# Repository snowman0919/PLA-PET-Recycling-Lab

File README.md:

# PPR — 균일 직경 필라멘트를 위한 통합 재활용기
목표와 경계는 [KODEX.md](KODEX.md), 현재 증거·작업은 [STATUS.md](STATUS.md), 압출 방법 비교는 [품질 경로 결정 기록](docs/decisions/filament-quality-route.md)을 따른다.

제품 범위: 호퍼 → S1 2축 파쇄 → 선택 이송부 → S2 편심/역자전 분쇄 → 버퍼 → 수평 압출 → 냉각/직경 계측 → 가압 인출 → 장력 분리 권취.
최종 목표는 냉각 후 일정한 1.75mm 필라멘트를 경제적으로 만드는 것이다. 현재 연결 이송과 실제 필라멘트 생산 모두 미완료다.
상류 실패와 별개로 최종 제품의 같은 압출 모듈에 건조 기준 원료를 넣는 설계/디지털 시험을 진행할 수 있다. 전체 제품 성공과는 구분한다.

## 작업 자산
- c2.1/cad/PPR_VP1.step: 전체 기계 STEP
- c2.1/cad/PPR_C2_1_machine_integration.FCStd 및 c2.1/src/: 편집 원본/생성기
- c2.1/bom/system_bom.csv, .xlsx: 활성 BOM
- c2.1/firmware/, electrical/: 제어/전장 자산
- c2.2/sim/assets/usd/full_machine.usda: 대응 Isaac 장면
- c2.2/results/full_machine/layout_comparison.json: 기준안/재배치안 비교
- tests/, c2/tests/, c2.1/tests/, c2.3/tests/: 범위별 회귀 자산

재현은 해당 생성기/실행기의 --help와 결과의 원본 해시·설정을 사용한다. CAD/STEP, 충돌 메시/USD, BOM, 시험 결과를 같은 후보로 맞춘 후 해당 verify_artifacts를 수행한다.
역사 실험의 재실행이나 Graphify 완료를 새 제품 작업의 선행조건으로 만들지 않는다. 숫자·PASS 명칭은 당시 범위에서만 유효하다.
물리 제작·구매·통전·실물시험·main 병합은 사용자 승인 전 HOLD다. MIT 및 LICENSE-HARDWARE를 유지한다.

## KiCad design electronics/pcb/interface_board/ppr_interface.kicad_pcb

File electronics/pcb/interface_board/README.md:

# PPR monitor/interface board

`ppr_interface.kicad_sch`와 `ppr_interface.kicad_pcb`는 KiCad 9 네이티브 산출물이다. `generate.py`가 source of truth이며 `fill_zones.py`는 KiCad의 pcbnew 엔진으로 분리된 FIELD_0V/GND 존을 채운다.

이 보드는 **MONITOR ONLY / NO SAFETY CREDIT / NOT FOR FABRICATION** 상태다. 안전 릴레이, 접촉기, 퓨즈, thermal fuse, heater/motor driver를 대체하지 않는다.

## 재생성

```bash
python3 -m venv /tmp/ppr-kiutils-venv
/tmp/ppr-kiutils-venv/bin/pip install -r electronics/pcb/interface_board/requirements-authoring.txt
/tmp/ppr-kiutils-venv/bin/python electronics/pcb/interface_board/generate.py
kicad-cli sch erc --exit-code-violations electronics/pcb/interface_board/ppr_interface.kicad_sch
kicad-cli pcb drc --exit-code-violations electronics/pcb/interface_board/ppr_interface.kicad_pcb
```

필수 도구는 KiCad CLI/pcbnew 9.0.9와 `kiutils==1.4.8`이다. 회로·PCB 검토 결과는 `design_review_ko.md`, 공식 URL/로컬 검토 해시는 `datasheet_evidence.json`, 제조 출력은 `fabrication/`, 육안 검토 렌더는 `review/`에 있다. 제3자 PDF 자체는 루트 정책에 따라 Git에 넣지 않는다.

## 인터페이스

- J1: 8개 24 V dry-contact 보조 입력과 중복 +24V_SENSE/FIELD_0V
- J2: Mega D22–D29 진단 입력
- J3: Mega command 입력 8개
- J4: 외부 정격 드라이버로 가는 5 V 로직 출력 8개

정확한 케이블 결선은 `design_review_ko.md`와 `electronics/pinout/mega_pinout.csv`를 함께 사용한다. 현재 pin header footprint는 기구 proof용이며 keyed/latching 커넥터 MPN 확정 전 발주 금지다.

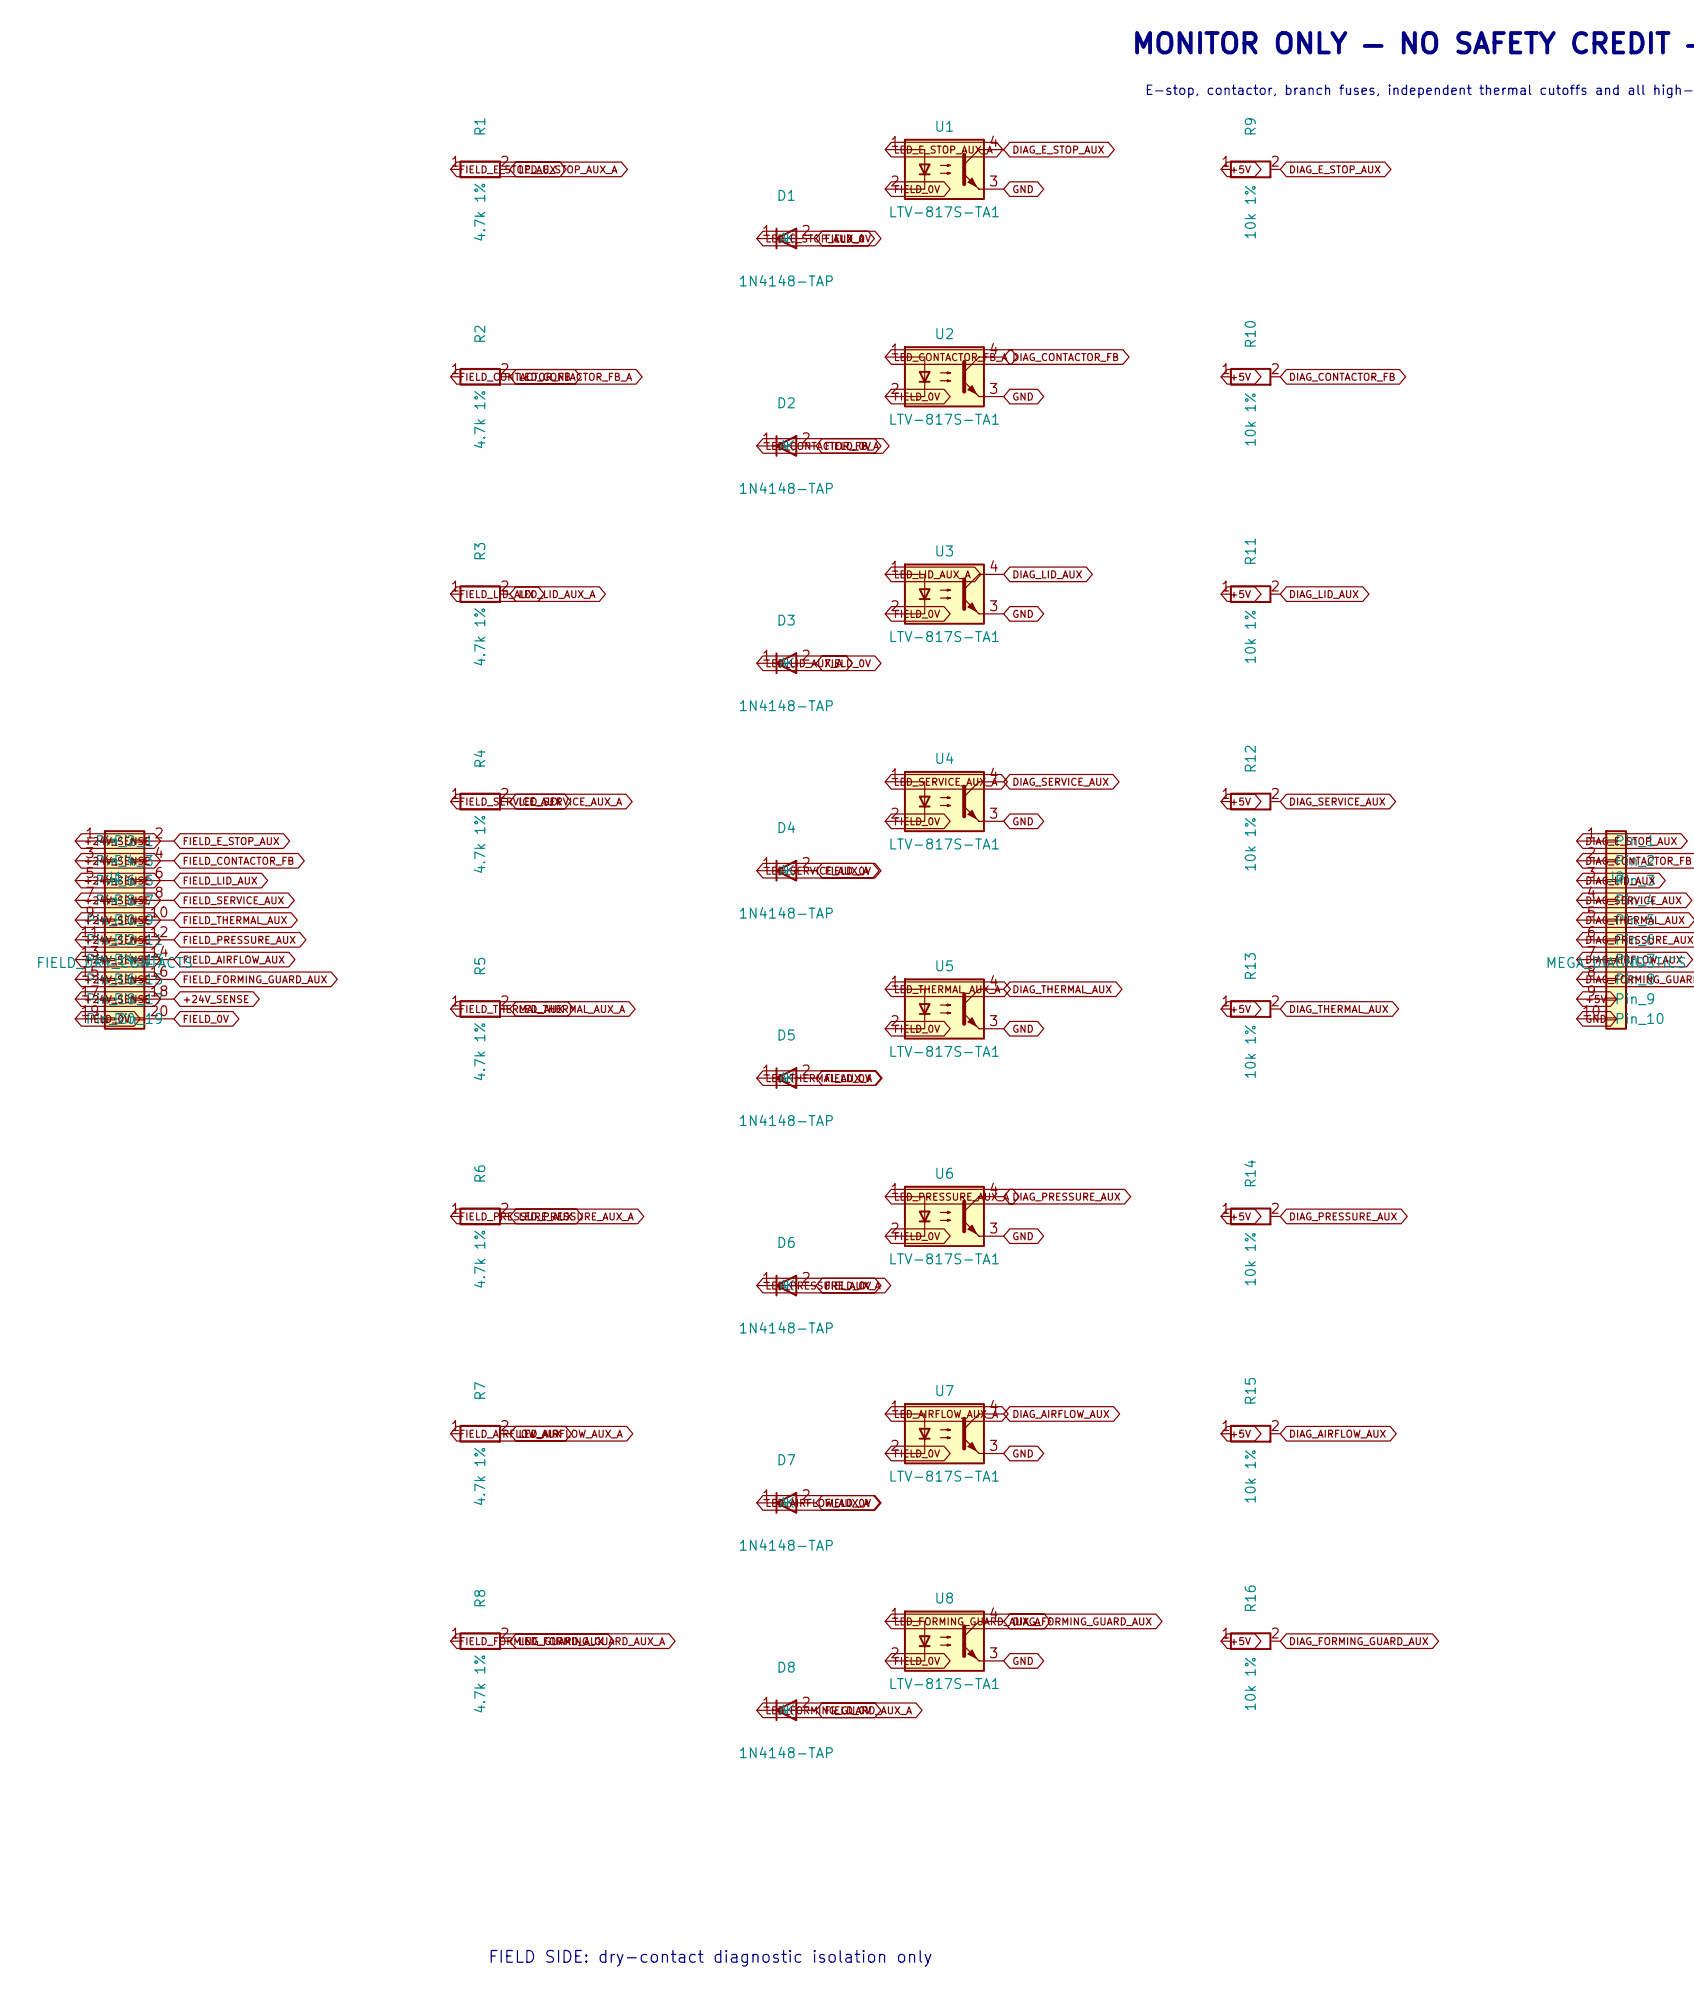
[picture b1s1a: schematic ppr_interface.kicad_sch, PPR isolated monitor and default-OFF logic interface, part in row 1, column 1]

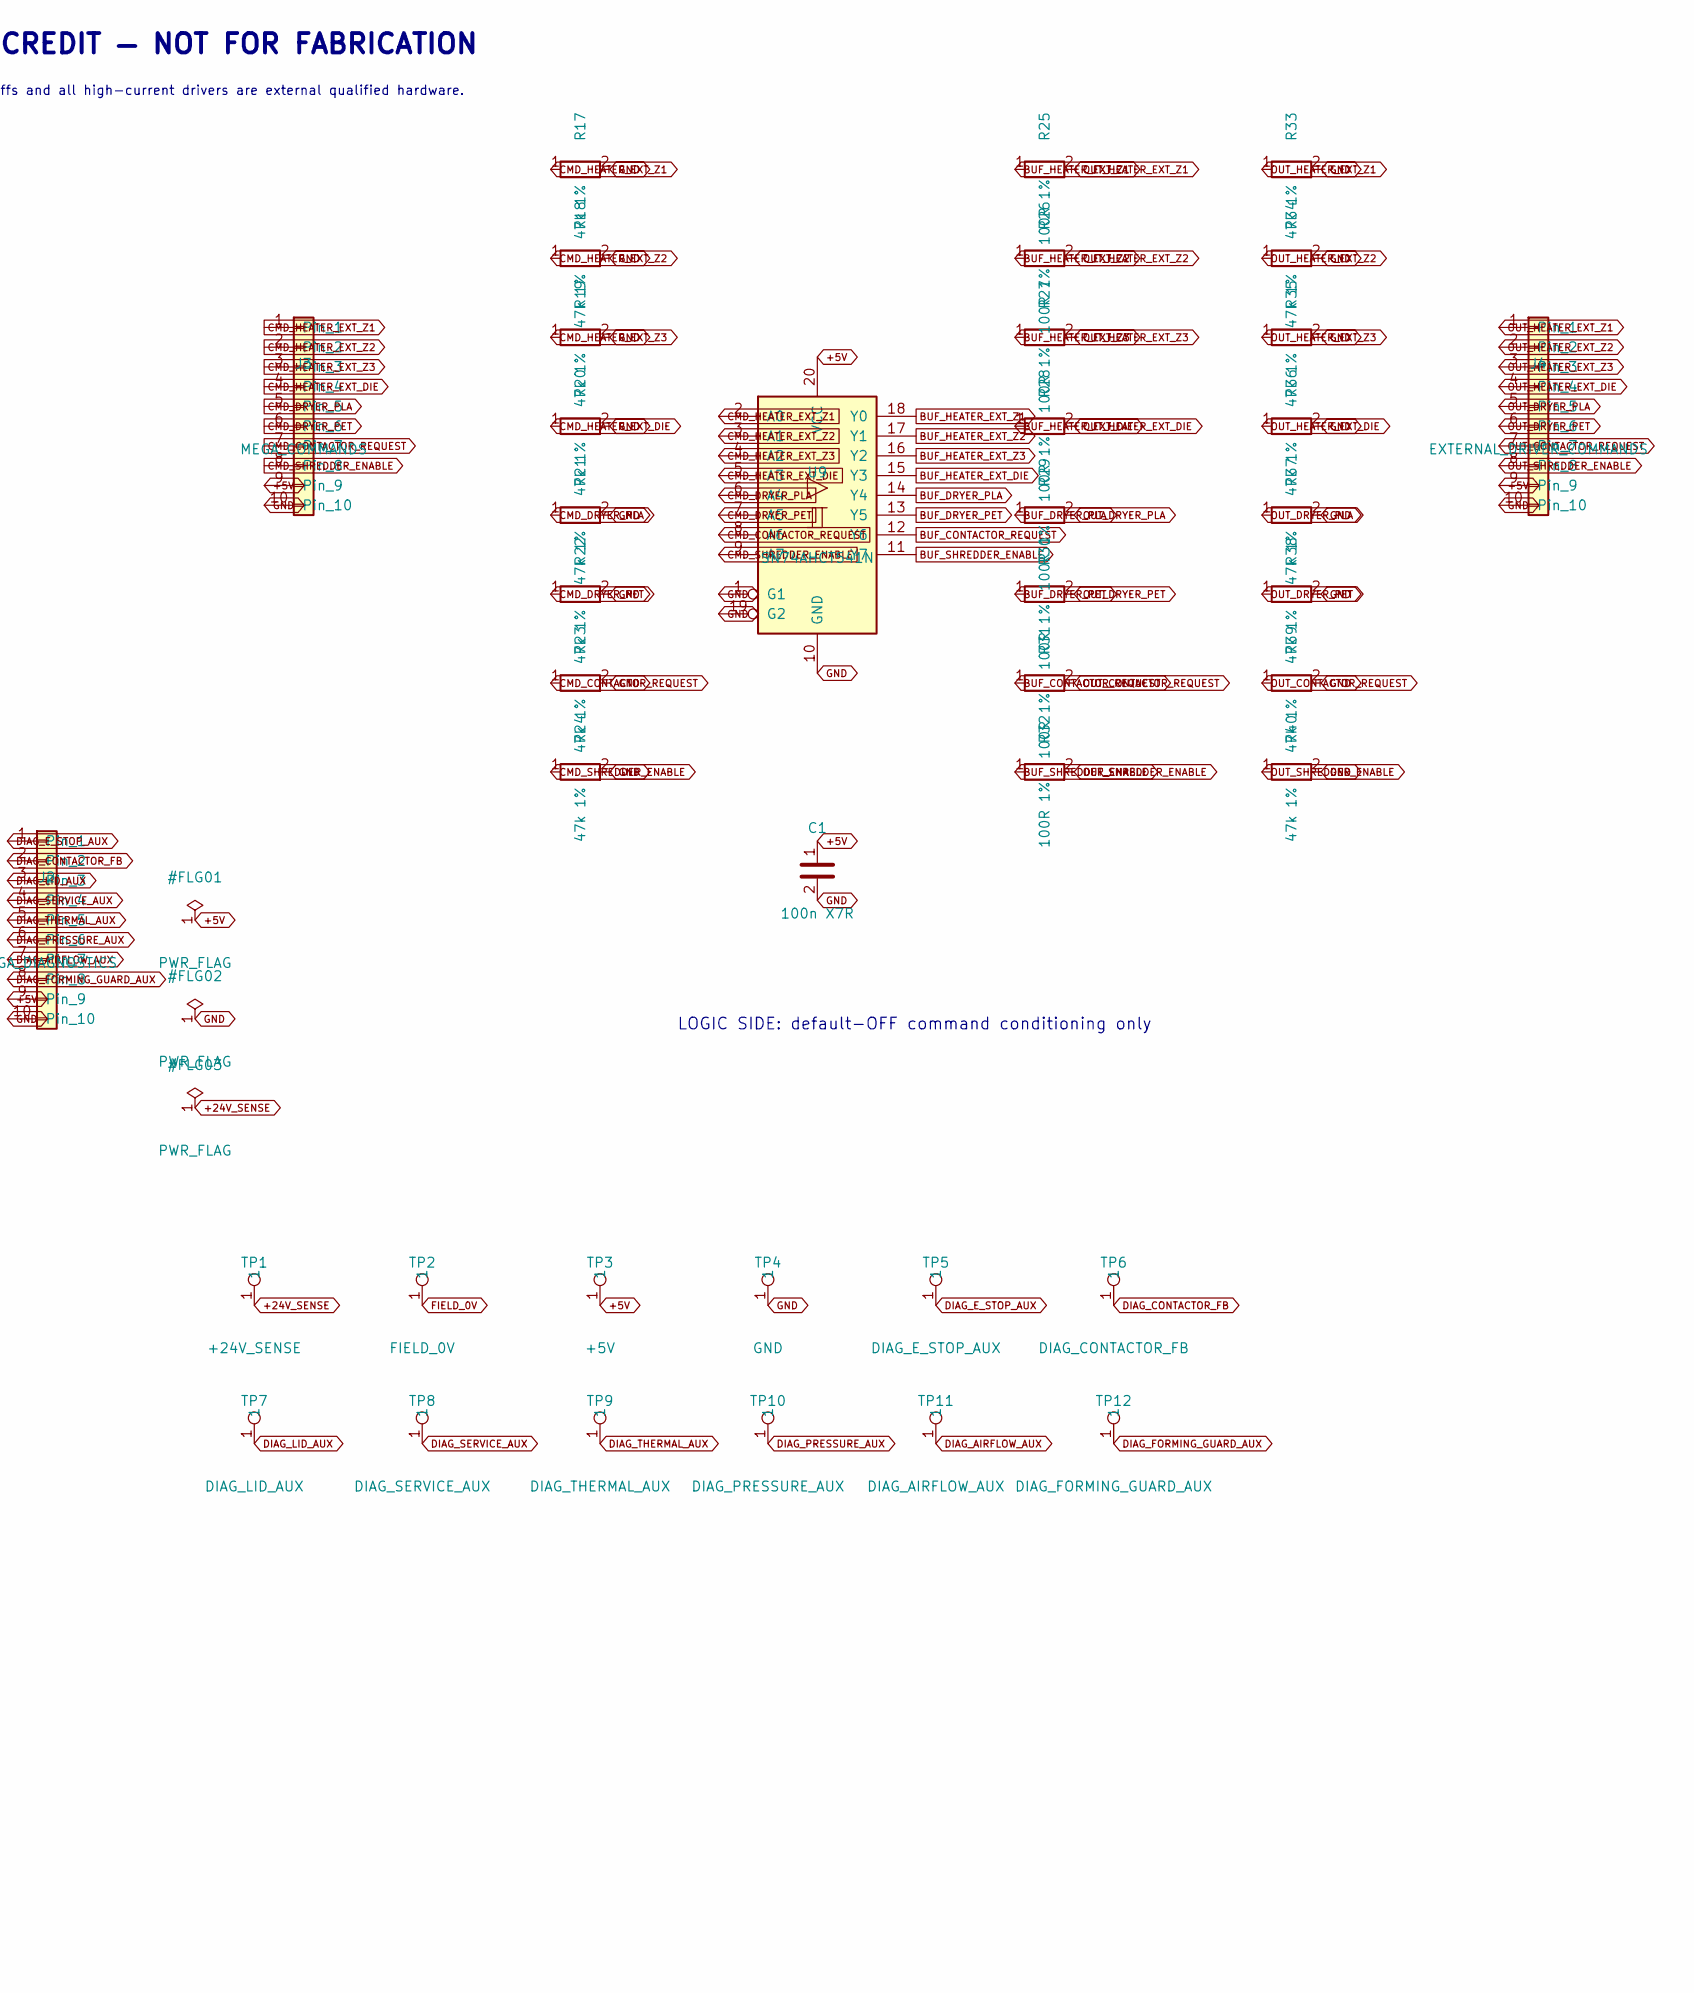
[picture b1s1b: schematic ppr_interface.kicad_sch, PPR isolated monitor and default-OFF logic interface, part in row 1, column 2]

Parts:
C1: 100n X7R; C_Disc_D5.0mm_W2.5mm_P2.50mm; MPN TBD
D1, D2, D3, D4, D5, D6, D7, D8: 1N4148-TAP; D_DO-35_SOD27_P7.62mm_Horizontal; MPN 1N4148-TAP
J1: FIELD_DRY_CONTACTS; PinHeader_2x10_P2.54mm_Vertical; MPN TBD
J2: MEGA_DIAGNOSTICS; PinHeader_1x10_P2.54mm_Vertical; MPN TBD
J3: MEGA_COMMANDS; PinHeader_1x10_P2.54mm_Vertical; MPN TBD
J4: EXTERNAL_DRIVER_COMMANDS; PinHeader_1x10_P2.54mm_Vertical; MPN TBD
R1, R2, R3, R4, R5, R6, R7, R8: 4.7k 1%; R_Axial_DIN0207_L6.3mm_D2.5mm_P10.16mm_Horizontal; MPN TBD
R9, R10, R11, R12, R13, R14, R15, R16: 10k 1%; R_Axial_DIN0207_L6.3mm_D2.5mm_P10.16mm_Horizontal; MPN TBD
R17, R18, R19, R20, R21, R22, R23, R24, R33, R34, R35, R36, R37, R38, R39, R40: 47k 1%; R_Axial_DIN0207_L6.3mm_D2.5mm_P10.16mm_Horizontal; MPN TBD
R25, R26, R27, R28, R29, R30, R31, R32: 100R 1%; R_Axial_DIN0207_L6.3mm_D2.5mm_P10.16mm_Horizontal; MPN TBD
TP1: +24V_SENSE; TestPoint_THTPad_D3.0mm_Drill1.5mm; MPN TBD
TP2: FIELD_0V; TestPoint_THTPad_D3.0mm_Drill1.5mm; MPN TBD
TP3: +5V; TestPoint_THTPad_D3.0mm_Drill1.5mm; MPN TBD
TP4: GND; TestPoint_THTPad_D3.0mm_Drill1.5mm; MPN TBD
TP5: DIAG_E_STOP_AUX; TestPoint_THTPad_D3.0mm_Drill1.5mm; MPN TBD
TP6: DIAG_CONTACTOR_FB; TestPoint_THTPad_D3.0mm_Drill1.5mm; MPN TBD
TP7: DIAG_LID_AUX; TestPoint_THTPad_D3.0mm_Drill1.5mm; MPN TBD
TP8: DIAG_SERVICE_AUX; TestPoint_THTPad_D3.0mm_Drill1.5mm; MPN TBD
TP9: DIAG_THERMAL_AUX; TestPoint_THTPad_D3.0mm_Drill1.5mm; MPN TBD
TP10: DIAG_PRESSURE_AUX; TestPoint_THTPad_D3.0mm_Drill1.5mm; MPN TBD
TP11: DIAG_AIRFLOW_AUX; TestPoint_THTPad_D3.0mm_Drill1.5mm; MPN TBD
TP12: DIAG_FORMING_GUARD_AUX; TestPoint_THTPad_D3.0mm_Drill1.5mm; MPN TBD
U1, U2, U3, U4, U5, U6, U7, U8: LTV-817S-TA1; SMDIP-4_W9.53mm; MPN LTV-817S-TA1
U9: SN74AHCT541N; DIP-20_W7.62mm_LongPads; MPN SN74AHCT541N

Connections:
+5V: C1.1, J2.9, J3.9, J4.9, R9.1, R10.1, R11.1, R12.1, R13.1, R14.1, R15.1, R16.1, TP3.1, U9.20 (VCC)
+24V_SENSE: J1.1, J1.3, J1.5, J1.7, J1.9, J1.11, J1.13, J1.15, J1.17, J1.18, TP1.1
BUF_CONTACTOR_REQUEST: R31.1, U9.12 (Y6)
BUF_DRYER_PET: R30.1, U9.13 (Y5)
BUF_DRYER_PLA: R29.1, U9.14 (Y4)
BUF_HEATER_EXT_DIE: R28.1, U9.15 (Y3)
BUF_HEATER_EXT_Z1: R25.1, U9.18 (Y0)
BUF_HEATER_EXT_Z2: R26.1, U9.17 (Y1)
BUF_HEATER_EXT_Z3: R27.1, U9.16 (Y2)
BUF_SHREDDER_ENABLE: R32.1, U9.11 (Y7)
CMD_CONTACTOR_REQUEST: J3.7, R23.1, U9.8 (A6)
CMD_DRYER_PET: J3.6, R22.1, U9.7 (A5)
CMD_DRYER_PLA: J3.5, R21.1, U9.6 (A4)
CMD_HEATER_EXT_DIE: J3.4, R20.1, U9.5 (A3)
CMD_HEATER_EXT_Z1: J3.1, R17.1, U9.2 (A0)
CMD_HEATER_EXT_Z2: J3.2, R18.1, U9.3 (A1)
CMD_HEATER_EXT_Z3: J3.3, R19.1, U9.4 (A2)
CMD_SHREDDER_ENABLE: J3.8, R24.1, U9.9 (A7)
DIAG_AIRFLOW_AUX: J2.7, R15.2, TP11.1, U7.4
DIAG_CONTACTOR_FB: J2.2, R10.2, TP6.1, U2.4
DIAG_E_STOP_AUX: J2.1, R9.2, TP5.1, U1.4
DIAG_FORMING_GUARD_AUX: J2.8, R16.2, TP12.1, U8.4
DIAG_LID_AUX: J2.3, R11.2, TP7.1, U3.4
DIAG_PRESSURE_AUX: J2.6, R14.2, TP10.1, U6.4
DIAG_SERVICE_AUX: J2.4, R12.2, TP8.1, U4.4
DIAG_THERMAL_AUX: J2.5, R13.2, TP9.1, U5.4
FIELD_0V: D1.2 (A), D2.2 (A), D3.2 (A), D4.2 (A), D5.2 (A), D6.2 (A), D7.2 (A), D8.2 (A), J1.19, J1.20, TP2.1, U1.2, U2.2, U3.2, U4.2, U5.2, U6.2, U7.2, U8.2
FIELD_AIRFLOW_AUX: J1.14, R7.1
FIELD_CONTACTOR_FB: J1.4, R2.1
FIELD_E_STOP_AUX: J1.2, R1.1
FIELD_FORMING_GUARD_AUX: J1.16, R8.1
FIELD_LID_AUX: J1.6, R3.1
FIELD_PRESSURE_AUX: J1.12, R6.1
FIELD_SERVICE_AUX: J1.8, R4.1
FIELD_THERMAL_AUX: J1.10, R5.1
GND: C1.2, J2.10, J3.10, J4.10, R17.2, R18.2, R19.2, R20.2, R21.2, R22.2, R23.2, R24.2, R33.2, R34.2, R35.2, R36.2, R37.2, R38.2, R39.2, R40.2, TP4.1, U1.3, U2.3, U3.3, U4.3, U5.3, U6.3, U7.3, U8.3, U9.1 (G1), U9.10 (GND), U9.19 (G2)
LED_AIRFLOW_AUX_A: D7.1 (K), R7.2, U7.1
LED_CONTACTOR_FB_A: D2.1 (K), R2.2, U2.1
LED_E_STOP_AUX_A: D1.1 (K), R1.2, U1.1
LED_FORMING_GUARD_AUX_A: D8.1 (K), R8.2, U8.1
LED_LID_AUX_A: D3.1 (K), R3.2, U3.1
LED_PRESSURE_AUX_A: D6.1 (K), R6.2, U6.1
LED_SERVICE_AUX_A: D4.1 (K), R4.2, U4.1
LED_THERMAL_AUX_A: D5.1 (K), R5.2, U5.1
OUT_CONTACTOR_REQUEST: J4.7, R31.2, R39.1
OUT_DRYER_PET: J4.6, R30.2, R38.1
OUT_DRYER_PLA: J4.5, R29.2, R37.1
OUT_HEATER_EXT_DIE: J4.4, R28.2, R36.1
OUT_HEATER_EXT_Z1: J4.1, R25.2, R33.1
OUT_HEATER_EXT_Z2: J4.2, R26.2, R34.1
OUT_HEATER_EXT_Z3: J4.3, R27.2, R35.1
OUT_SHREDDER_ENABLE: J4.8, R32.2, R40.1

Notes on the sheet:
MONITOR ONLY — NO SAFETY CREDIT — NOT FOR FABRICATION
E-stop, contactor, branch fuses, independent thermal cutoffs and all high-current drivers are external qualified hardware.
FIELD SIDE: dry-contact diagnostic isolation only
LOGIC SIDE: default-OFF command conditioning only

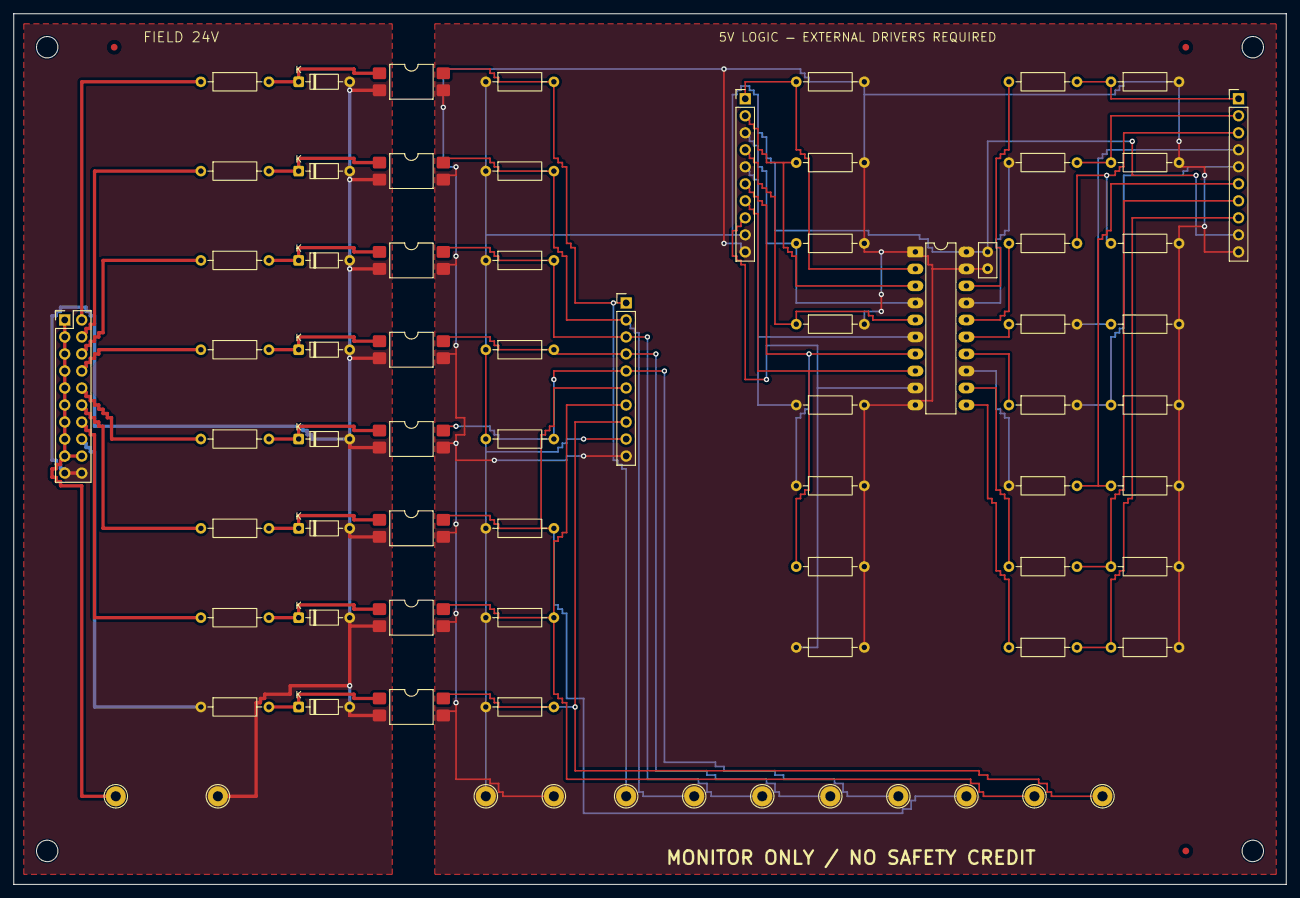
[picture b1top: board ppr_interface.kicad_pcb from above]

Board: 2 copper layers, 190.0 x 130.0 mm, 81 parts (0 on the bottom side), 52 nets.

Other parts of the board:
FID1, FID2, FID3: FIDUCIAL_1MM; Fiducial_1mm_Mask2mm
H1, H2, H3, H4: M3_NPTH; MountingHole_3.2mm_M3

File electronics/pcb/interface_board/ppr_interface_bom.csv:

"Reference","Value","Footprint","Manufacturer","MPN","Datasheet","Sourcing","Comments","Quantity"
"C1","100n X7R","Capacitor_THT:C_Disc_D5.0mm_W2.5mm_P2.50mm","TBD","TBD","~","BUY","","1"
"D1-D8","1N4148-TAP","Diode_THT:D_DO-35_SOD27_P7.62mm_Horizontal","Vishay","1N4148-TAP","https://www.vishay.com/docs/81857/1n4148.pdf","BUY","","8"
"J1","FIELD_DRY_CONTACTS","Connector_PinHeader_2.54mm:PinHeader_2x10_P2.54mm_Vertical","TBD","TBD","~","BUY","","1"
"J2","MEGA_DIAGNOSTICS","Connector_PinHeader_2.54mm:PinHeader_1x10_P2.54mm_Vertical","TBD","TBD","~","BUY","","1"
"J3","MEGA_COMMANDS","Connector_PinHeader_2.54mm:PinHeader_1x10_P2.54mm_Vertical","TBD","TBD","~","BUY","","1"
"J4","EXTERNAL_DRIVER_COMMANDS","Connector_PinHeader_2.54mm:PinHeader_1x10_P2.54mm_Vertical","TBD","TBD","~","BUY","","1"
"R1-R8","4.7k 1%","Resistor_THT:R_Axial_DIN0207_L6.3mm_D2.5mm_P10.16mm_Horizontal","TBD","TBD","~","BUY","","8"
"R9-R16","10k 1%","Resistor_THT:R_Axial_DIN0207_L6.3mm_D2.5mm_P10.16mm_Horizontal","TBD","TBD","~","BUY","","8"
"R17-R24,R33-R40","47k 1%","Resistor_THT:R_Axial_DIN0207_L6.3mm_D2.5mm_P10.16mm_Horizontal","TBD","TBD","~","BUY","","16"
"R25-R32","100R 1%","Resistor_THT:R_Axial_DIN0207_L6.3mm_D2.5mm_P10.16mm_Horizontal","TBD","TBD","~","BUY","","8"
"U1-U8","LTV-817S-TA1","Package_DIP:SMDIP-4_W9.53mm","Lite-On","LTV-817S-TA1","https://optoelectronics.liteon.com/upload/download/DS-70-96-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","BUY","","8"
"U9","SN74AHCT541N","Package_DIP:DIP-20_W7.62mm_LongPads","Texas Instruments","SN74AHCT541N","https://www.ti.com/lit/ds/symlink/sn74ahct541.pdf","BUY","","1"

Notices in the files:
electronics/pcb/interface_board/ppr_interface.kicad_pcb:
PPR — CERN-OHL-P-2.0
